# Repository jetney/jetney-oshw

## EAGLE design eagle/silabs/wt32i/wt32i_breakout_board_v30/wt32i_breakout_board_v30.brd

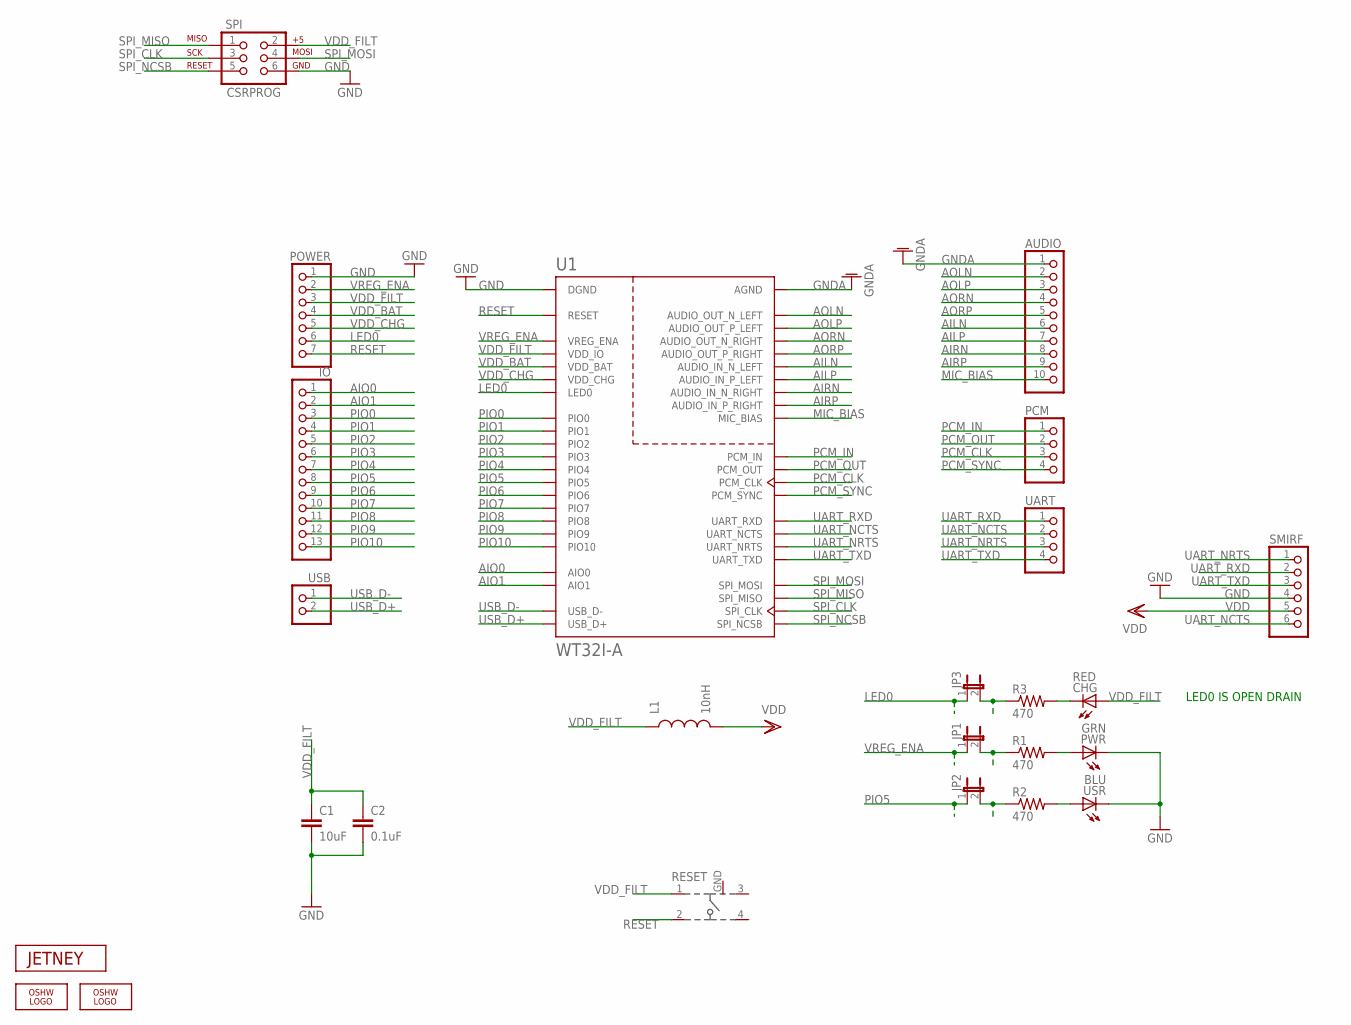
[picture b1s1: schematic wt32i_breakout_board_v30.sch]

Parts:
AUDIO: PINHD-1X10; 1X10
C1: 10uF; 0603-CAP
C2: 0.1uF; 0603-CAP
CHG: RED; CHIPLED_0805
IO: PINHD-1X13; 1X13
JP1, JP2, JP3: JUMPER-2SMD-NC; SJ_2S
L1: 10nH; 0603
LOGO1, LOGO2: OSHW_LOGO_FILLX0070-NT; OSHW_FILLX70_NOTEXT
PCM: PINHD-1X4; 1X04
POWER: PINHD-1X7; 1X07
PWR: GRN; CHIPLED_0805
R1, R2, R3: 470; 0603-RES
RESET: 101-IG
SMIRF: PINHD-1X6; 1X06
SPI: CSRPROG; 2X3
U1: WT32I-A
U$2: JETNEY-LOGO-12
UART: PINHD-1X4; 1X04
USB: PINHD-1X2; 1X02
USR: BLU; CHIPLED_0805

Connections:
AILN: AUDIO.6, U1.AUDIO_IN_N_LEFT
AILP: AUDIO.7, U1.AUDIO_IN_P_LEFT
AIO0: IO.1, U1.AIO0
AIO1: IO.2, U1.AIO1
AIRN: AUDIO.8, U1.AUDIO_IN_N_RIGHT
AIRP: AUDIO.9, U1.AUDIO_IN_P_RIGHT
AOLN: AUDIO.2, U1.AUDIO_OUT_N_LEFT
AOLP: AUDIO.3, U1.AUDIO_OUT_P_LEFT
AORN: AUDIO.4, U1.AUDIO_OUT_N_RIGHT
AORP: AUDIO.5, U1.AUDIO_OUT_P_RIGHT
GND: C1.2, C2.2, POWER.1, PWR.C, RESET.GND, SMIRF.4, SPI.6, U1.DGND, U1.DGND@2 (DGND), U1.DGND@3 (DGND), U1.DGND@4 (DGND), U1.DGND@5 (DGND), USR.C
GNDA: AUDIO.1, U1.AGND, U1.AGND@2 (AGND), U1.AGND@3 (AGND)
LED0: JP3.1, POWER.6, U1.LED0
MIC_BIAS: AUDIO.10, U1.MIC_BIAS
unnamed: PWR.A, R1.2
unnamed: CHG.C, R3.2
unnamed: R2.2, USR.A
unnamed: JP2.2, R2.1
unnamed: JP3.2, R3.1
PCM_CLK: PCM.3, U1.PCM_CLK
PCM_IN: PCM.1, U1.PCM_IN
PCM_OUT: PCM.2, U1.PCM_OUT
PCM_SYNC: PCM.4, U1.PCM_SYNC
PIO0: IO.3, U1.PIO0
PIO1: IO.4, U1.PIO1
PIO2: IO.5, U1.PIO2
PIO3: IO.6, U1.PIO3
PIO4: IO.7, U1.PIO4
PIO5: IO.8, JP2.1, U1.PIO5
PIO6: IO.9, U1.PIO6
PIO7: IO.10, U1.PIO7
PIO8: IO.11, U1.PIO8
PIO9: IO.12, U1.PIO9
PIO10: IO.13, U1.PIO10
RESET: POWER.7, RESET.2, U1.RESET
SPI_CLK: SPI.3, U1.SPI_CLK
SPI_MISO: SPI.1, U1.SPI_MISO
SPI_MOSI: SPI.4, U1.SPI_MOSI
SPI_NCSB: SPI.5, U1.SPI_NCSB
UART_NCTS: SMIRF.6, U1.UART_NCTS, UART.2
UART_NRTS: SMIRF.1, U1.UART_NRTS, UART.3
UART_RXD: SMIRF.2, U1.UART_RXD, UART.1
UART_TXD: SMIRF.3, U1.UART_TXD, UART.4
USB_D+: U1.USB_D+, USB.2
USB_D-: U1.USB_D-, USB.1
VDD: L1.2, SMIRF.5
VDDJP1: JP1.2, R1.1
VDD_BAT: POWER.4, U1.VDD_BAT
VDD_CHG: POWER.5, U1.VDD_CHG
VDD_FILT: C1.1, C2.1, CHG.A, L1.1, POWER.3, RESET.1, SPI.2, U1.VDD_IO
VREG_ENA: JP1.1, POWER.2, U1.VREG_ENA

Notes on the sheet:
LED0 IS OPEN DRAIN

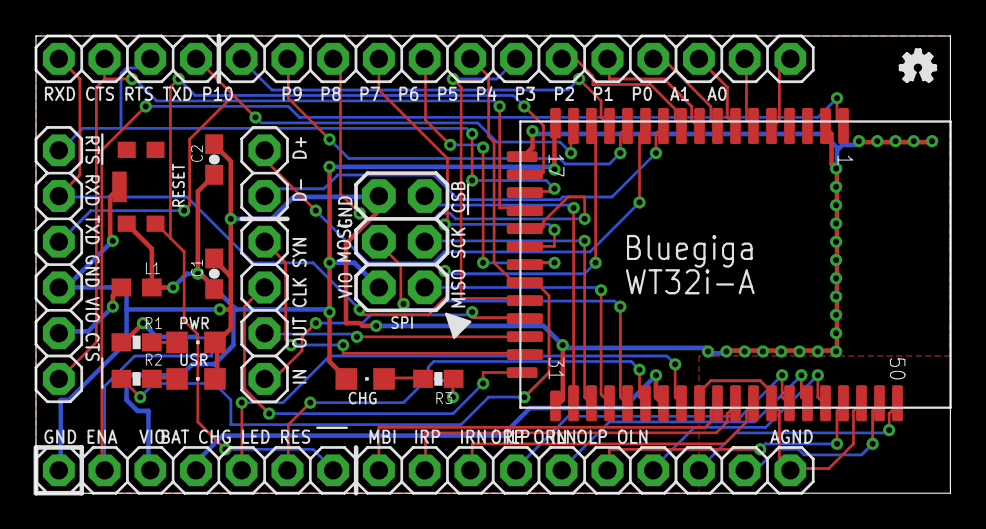
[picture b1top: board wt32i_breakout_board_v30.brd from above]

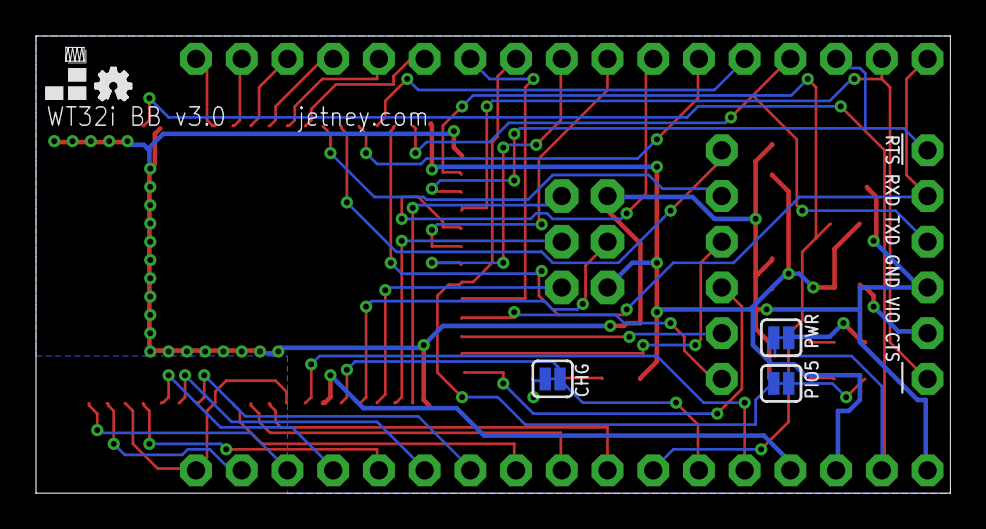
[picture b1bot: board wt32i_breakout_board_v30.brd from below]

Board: 2 copper layers, 50.8 x 25.4 mm, 25 parts (5 on the bottom side), 51 nets.

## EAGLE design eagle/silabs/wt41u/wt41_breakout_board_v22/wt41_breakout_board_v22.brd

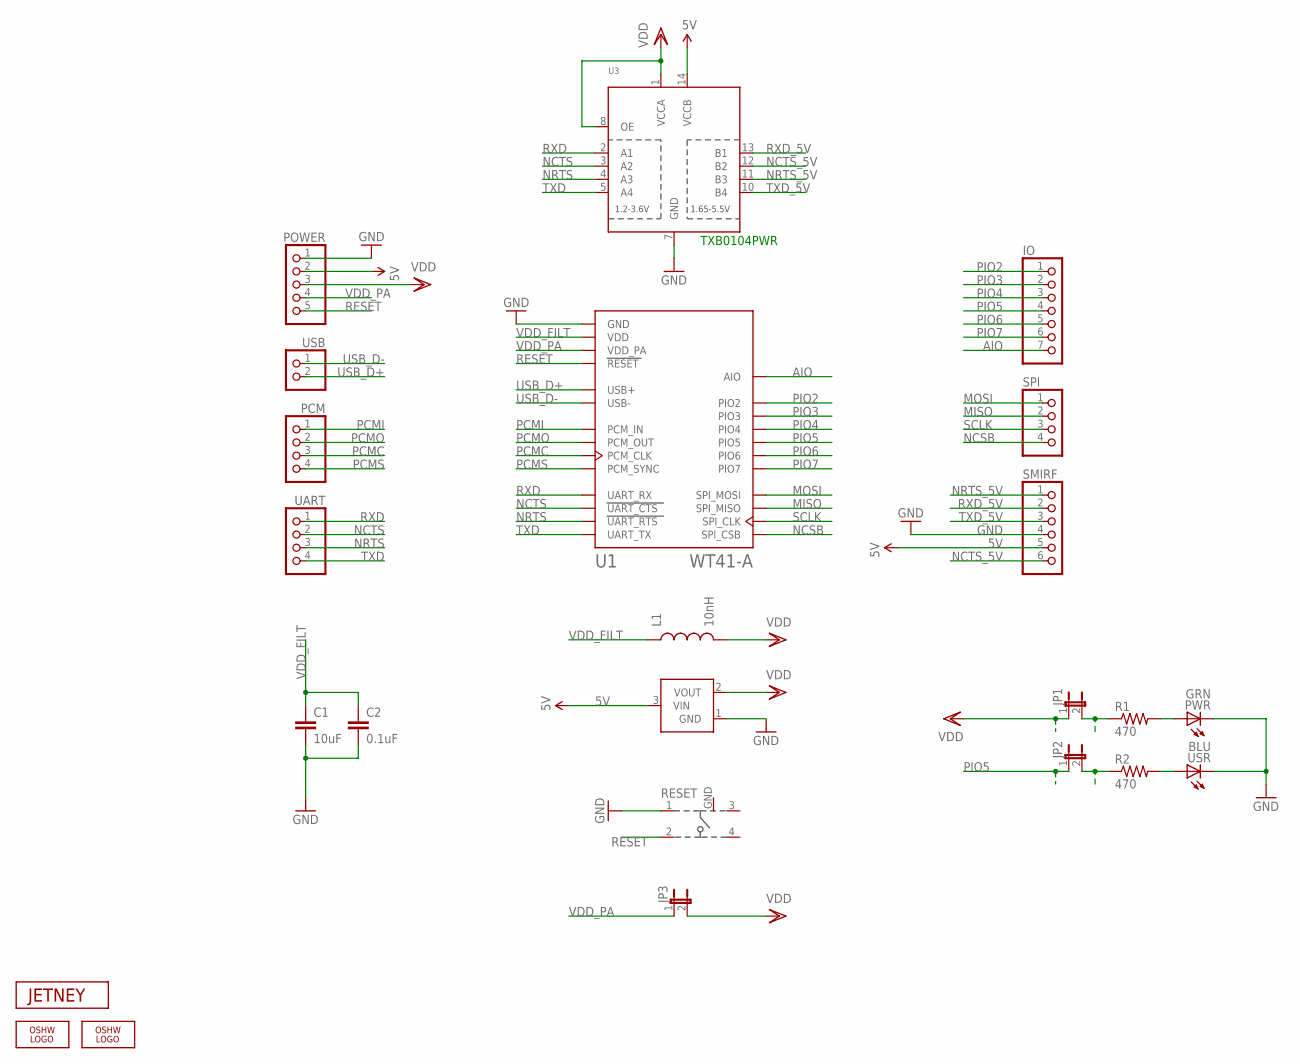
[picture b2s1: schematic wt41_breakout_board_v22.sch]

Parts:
C1: 10uF; 0603-CAP
C2: 0.1uF; 0603-CAP
IO: PINHD-1X7; 1X07
JP1, JP2, JP3: JUMPER-2SMD-NC; SJ_2S
L1: 10nH; 0603
LOGO1, LOGO2: OSHW_LOGO_FILLX0070-NT; OSHW_FILLX70_NOTEXT
PCM: PINHD-1X4; 1X04
POWER: PINHD-1X5; 1X05
PWR: GRN; CHIPLED_0805
R1, R2: 470; 0603-RES
RESET: 101-IG
SMIRF: PINHD-1X6; 1X06
SPI: PINHD-1X4; 1X04
U1: WT41-A
U2: MCP1700; SOT23-3
U3: TXB0104PWR; TSSOP14
U$2: JETNEY-LOGO-12
UART: PINHD-1X4; 1X04
USB: PINHD-1X2; 1X02
USR: BLU; CHIPLED_0805

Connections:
5V: POWER.2, SMIRF.5, U2.3 (VIN), U3.14 (VCCB)
AIO: IO.7, U1.AIO
GND: C1.2, C2.2, POWER.1, PWR.C, RESET.1, RESET.GND, SMIRF.4, U1.GND, U1.GND@2 (GND), U1.GND@3 (GND), U1.GND@4 (GND), U1.GND@5 (GND), U1.GND@6 (GND), U1.GND@7 (GND), U1.GND@8 (GND), U1.GND@9 (GND), U1.GND@10 (GND), U1.GND@11 (GND), U1.GND@12 (GND), U1.GND@13 (GND), U1.GND@14 (GND), U1.GND@15 (GND), U1.GND@16 (GND), U1.GND@17 (GND), U1.GND@18 (GND), U1.GND@19 (GND), U1.GND@20 (GND), U1.GND@21 (GND), U1.GND@22 (GND), U1.GND@23 (GND), U1.GND@24 (GND), U1.GND@25 (GND), U1.GND@26 (GND), U1.GND@27 (GND), U1.GND@28 (GND), U1.GND@29 (GND), U1.GND@30 (GND), U1.GND@31 (GND), U2.1 (GND), U3.7 (GND), USR.C
MISO: SPI.2, U1.SPI_MISO
MOSI: SPI.1, U1.SPI_MOSI
unnamed: PWR.A, R1.2
unnamed: R2.2, USR.A
unnamed: JP2.2, R2.1
NCSB: SPI.4, U1.SPI_CSB
NCTS: U1.UART_CTS, U3.3 (A2), UART.2
NCTS_5V: SMIRF.6, U3.12 (B2)
NRTS: U1.UART_RTS, U3.4 (A3), UART.3
NRTS_5V: SMIRF.1, U3.11 (B3)
PCMC: PCM.3, U1.PCM_CLK
PCMI: PCM.1, U1.PCM_IN
PCMO: PCM.2, U1.PCM_OUT
PCMS: PCM.4, U1.PCM_SYNC
PIO2: IO.1, U1.PIO2
PIO3: IO.2, U1.PIO3
PIO4: IO.3, U1.PIO4
PIO5: IO.4, JP2.1, U1.PIO5
PIO6: IO.5, U1.PIO6
PIO7: IO.6, U1.PIO7
RESET: POWER.5, RESET.2, U1.RESET
RXD: U1.UART_RX, U3.2 (A1), UART.1
RXD_5V: SMIRF.2, U3.13 (B1)
SCLK: SPI.3, U1.SPI_CLK
TXD: U1.UART_TX, U3.5 (A4), UART.4
TXD_5V: SMIRF.3, U3.10 (B4)
USB_D+: U1.USB+, USB.2
USB_D-: U1.USB-, USB.1
VDD: JP1.1, JP3.2, L1.2, POWER.3, U2.2 (VOUT), U3.1 (VCCA), U3.8 (OE)
VDDJP1: JP1.2, R1.1
VDD_FILT: C1.1, C2.1, L1.1, U1.VDD
VDD_PA: JP3.1, POWER.4, U1.VDD_PA

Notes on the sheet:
TXB0104PWR

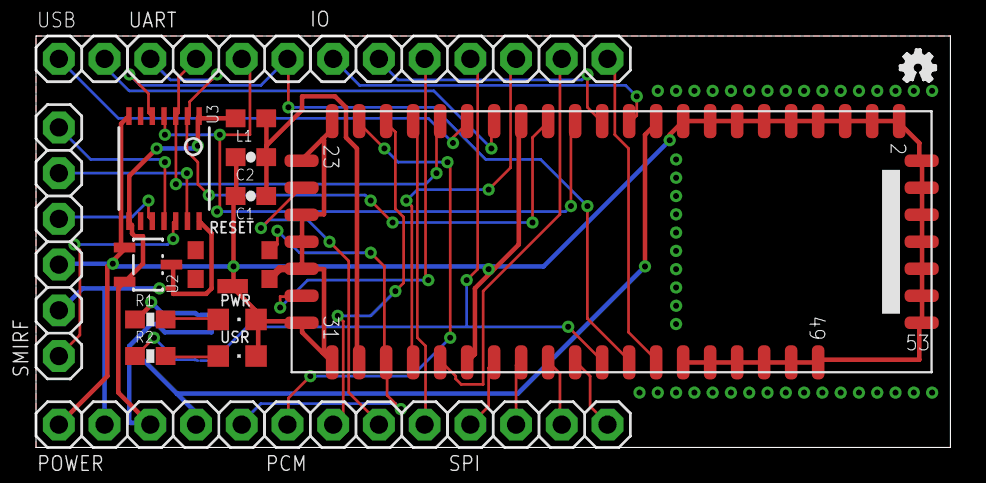
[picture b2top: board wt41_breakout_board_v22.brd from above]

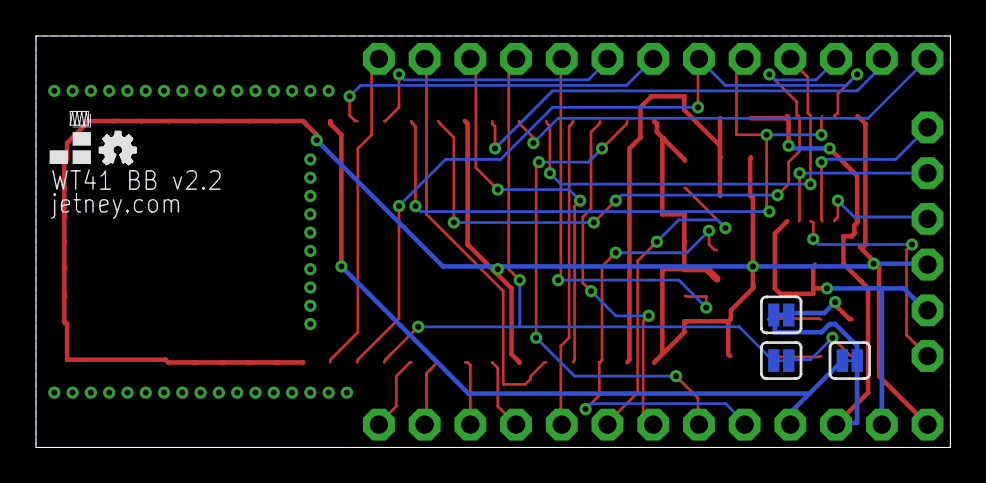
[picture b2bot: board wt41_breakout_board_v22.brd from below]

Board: 2 copper layers, 50.8 x 22.9 mm, 24 parts (5 on the bottom side), 35 nets.

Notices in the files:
parts and their libraries:
SparkFun: Licensing: CC v3.0 Share-Alike You are welcome to use this library for commercial purposes.
